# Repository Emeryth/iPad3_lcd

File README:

Schematics of an interface board for connecting an iPad retina display (LP097QX1-SPA1) to a DisplayPort source.

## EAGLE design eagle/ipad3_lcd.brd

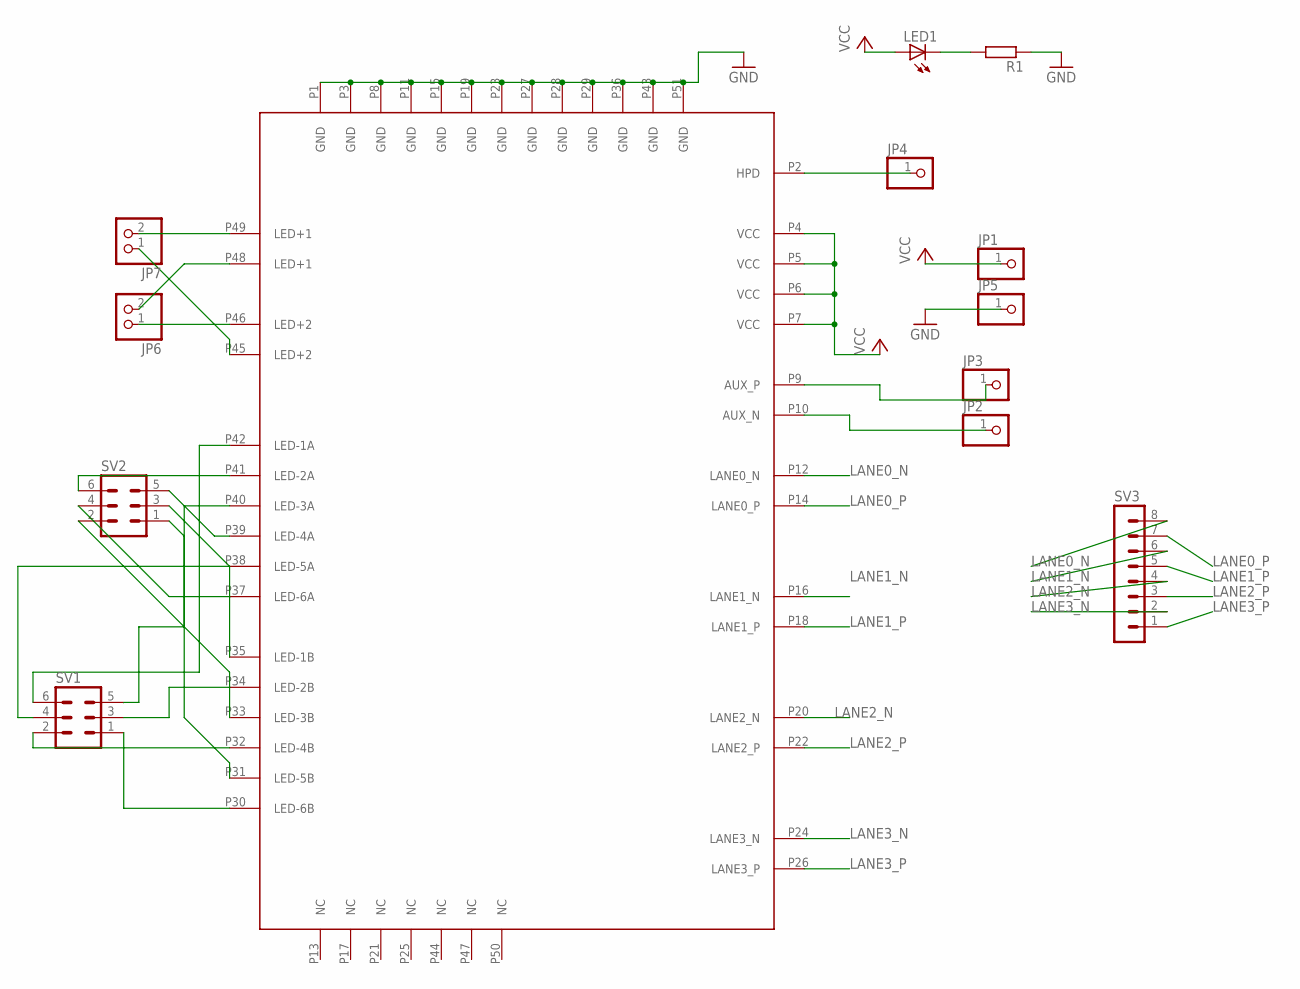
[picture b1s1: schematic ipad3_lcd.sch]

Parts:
JP1, JP2, JP3, JP4, JP5: PINHD-1X1; 1X01
JP6, JP7: PINHD-1X2; 1X02
LED1: LEDCHIP-LED0805; CHIP-LED0805
R1: R-EU_M0805; M0805
SV1, SV2: MA03-2
SV3: MA08-1
U$1: IPAD3-CONN; MOLEX502250-5191

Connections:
AUX_N: JP2.1, U$1.P10 (AUX_N)
AUX_P: JP3.1, U$1.P9 (AUX_P)
GND: JP5.1, R1.1, U$1.P1 (GND), U$1.P3 (GND), U$1.P8 (GND), U$1.P11 (GND), U$1.P15 (GND), U$1.P19 (GND), U$1.P23 (GND), U$1.P27 (GND), U$1.P28 (GND), U$1.P29 (GND), U$1.P36 (GND), U$1.P43 (GND), U$1.P51 (GND)
HPD: JP4.1, U$1.P2 (HPD)
LANE0_N: SV3.8, U$1.P12 (LANE0_N)
LANE0_P: SV3.7, U$1.P14 (LANE0_P)
LANE1_N: SV3.6, U$1.P16 (LANE1_N)
LANE1_P: SV3.5, U$1.P18 (LANE1_P)
LANE2_N: SV3.4, U$1.P20 (LANE2_N)
LANE2_P: SV3.3, U$1.P22 (LANE2_P)
LANE3_N: SV3.2, U$1.P24 (LANE3_N)
LANE3_P: SV3.1, U$1.P26 (LANE3_P)
unnamed: SV1.1, U$1.P30 (LED-6B)
unnamed: SV1.2, U$1.P32 (LED-4B)
unnamed: LED1.C, R1.2
unnamed: SV1.3, U$1.P34 (LED-2B)
unnamed: SV1.4, U$1.P38 (LED-5A)
unnamed: SV1.5, U$1.P40 (LED-3A)
unnamed: SV1.6, U$1.P42 (LED-1A)
unnamed: SV2.6, U$1.P41 (LED-2A)
unnamed: SV2.5, U$1.P39 (LED-4A)
unnamed: SV2.4, U$1.P37 (LED-6A)
unnamed: SV2.3, U$1.P35 (LED-1B)
unnamed: SV2.2, U$1.P33 (LED-3B)
unnamed: SV2.1, U$1.P31 (LED-5B)
unnamed: JP6.1, U$1.P46 (LED+2)
unnamed: JP6.2, U$1.P48 (LED+1)
unnamed: JP7.1, U$1.P45 (LED+2)
unnamed: JP7.2, U$1.P49 (LED+1)
VCC: JP1.1, LED1.A, U$1.P4 (VCC), U$1.P5 (VCC), U$1.P6 (VCC), U$1.P7 (VCC)

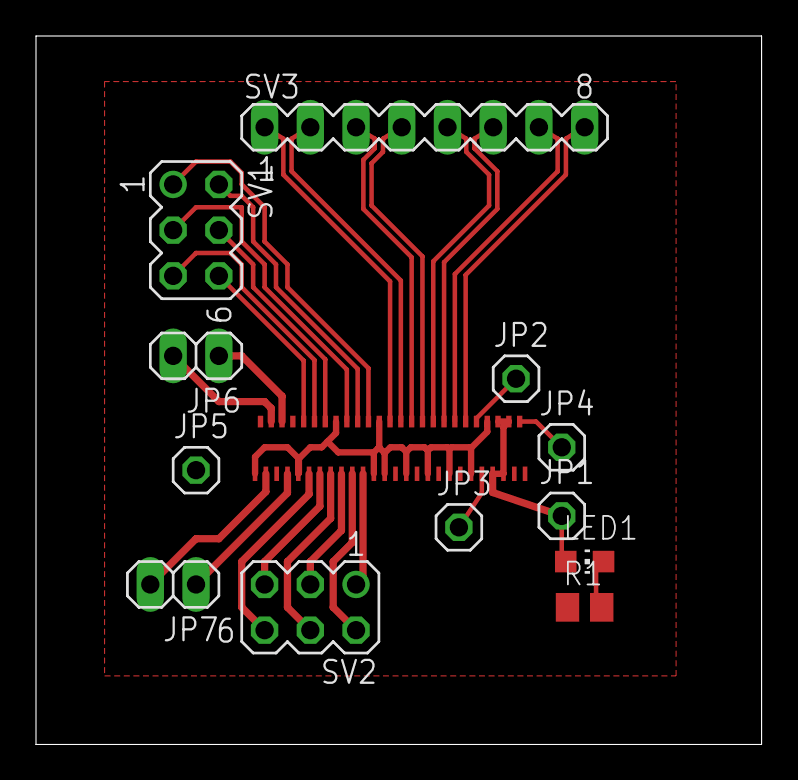
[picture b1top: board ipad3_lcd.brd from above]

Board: 2 copper layers, 40.3 x 39.4 mm, 13 parts (0 on the bottom side), 30 nets.

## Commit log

2013-04-20 Added readme
2013-05-05 New PCB in Kicad
2013-05-07 Board probably ready
2013-05-07 Changed outline width
2013-05-08 This version sent off to the fab
2013-06-01 Added Kicad design of new PCB. Reorganized the repo.
